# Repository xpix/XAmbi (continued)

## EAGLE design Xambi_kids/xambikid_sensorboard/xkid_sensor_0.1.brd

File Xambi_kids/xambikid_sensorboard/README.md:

XAmbi SensorBoard
----------------
By Frank Herrmann (xpixer@gmail.com)
<br/>

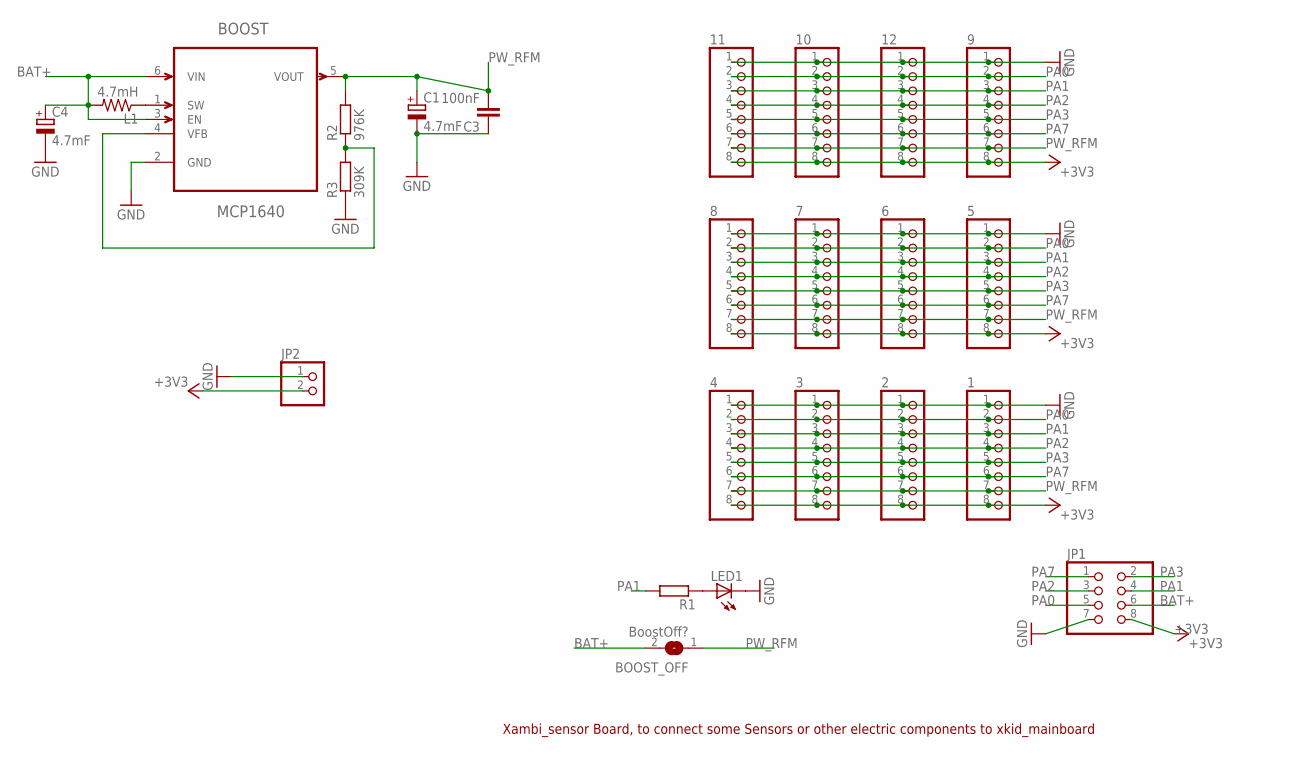
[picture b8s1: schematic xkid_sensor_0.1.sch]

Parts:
1, 2, 3, 4, 5, 6, 7, 8, 9, 10, 11, 12: PINHD-1X8_2.00; 1X08M
BOOST: MCP1640; SOT95P270X145-6N
BOOST_OFF: BoostOff?; SJ
C1, C4: 4.7mF; CT3216
C3: 100nF; C0805K
JP1: PINHD-2X4_2.54; 2X04
JP2: PINHD-1X2; 1X02
L1: 4.7mH; 0204/5
LED1: LEDCHIPLED_0805; CHIPLED_0805
R1: R-EU_R0805; R0805
R2: 976K; R0805
R3: 309K; R0805

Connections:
+3V3: 1.8, 2.8, 3.8, 4.8, 5.8, 6.8, 7.8, 8.8, 9.8, 10.8, 11.8, 12.8, JP1.8, JP2.2
BAT+: BOOST.3 (EN), BOOST.6 (VIN), BOOST_OFF.2, C4.+, JP1.6, L1.2
GND: 1.1, 2.1, 3.1, 4.1, 5.1, 6.1, 7.1, 8.1, 9.1, 10.1, 11.1, 12.1, BOOST.2 (GND), C1.-, C3.1, C4.-, JP1.7, JP2.1, LED1.C, R3.1
unnamed: LED1.A, R1.1
unnamed: BOOST.1 (SW), L1.1
unnamed: BOOST.4 (VFB), R2.1, R3.2
PA0: 1.2, 2.2, 3.2, 4.2, 5.2, 6.2, 7.2, 8.2, 9.2, 10.2, 11.2, 12.2, JP1.5
PA1: 1.3, 2.3, 3.3, 4.3, 5.3, 6.3, 7.3, 8.3, 9.3, 10.3, 11.3, 12.3, JP1.4, R1.2
PA2: 1.4, 2.4, 3.4, 4.4, 5.4, 6.4, 7.4, 8.4, 9.4, 10.4, 11.4, 12.4, JP1.3
PA3: 1.5, 2.5, 3.5, 4.5, 5.5, 6.5, 7.5, 8.5, 9.5, 10.5, 11.5, 12.5, JP1.2
PA7: 1.6, 2.6, 3.6, 4.6, 5.6, 6.6, 7.6, 8.6, 9.6, 10.6, 11.6, 12.6, JP1.1
PW_RFM: 1.7, 2.7, 3.7, 4.7, 5.7, 6.7, 7.7, 8.7, 9.7, 10.7, 11.7, 12.7, BOOST.5 (VOUT), BOOST_OFF.1, C1.+, C3.2, R2.2

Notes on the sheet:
Xambi_sensor Board, to connect some Sensors or other electric components to xkid_mainboard

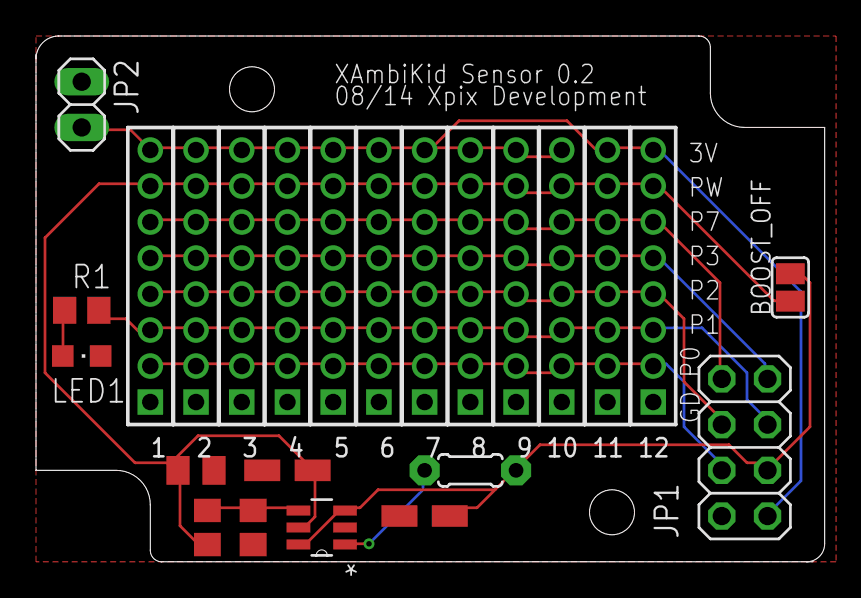
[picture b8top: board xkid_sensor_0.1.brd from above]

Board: 2 copper layers, 43.8 x 29.2 mm, 24 parts (0 on the bottom side), 12 nets.

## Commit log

2014-08-18 :tada: Added .gitattributes & .gitignore files
2014-08-18 Init commit
2015-01-08 Lot of updates
2015-01-08 Remove unused and temp files
2015-01-30 Lot of updates and new sensors
    - new mailbox sensor
    - update sensor mainboard
    - update sensor board
2015-01-30 Move old file to zip
2015-01-30 Remove some unused files
2015-01-30 add license
2015-02-02 add example schematic template for sensorboards
2015-02-02 Iniz readme for moisture board
2015-02-02 update example schema
2015-02-03 Fixes for mailbox and moisture sensor
    Change Threshold to 75 and calibrate every 15min and only 3 samples.
    Changes wait for minutes in moisture
2015-02-16 Last fixes for mailbox sensor
    - break 15 min and measure then (outside temp)
    - Threshold change to 40
    - display difference between calibration and measure value as second
    param
2015-03-02 fix and add docu for DS18B20
2015-03-02 add schematic for DHT11 Sensor
2015-03-03 - mailbox sensor doc and images
2015-03-03 Move not finished or ideas to prototype folder
2015-03-03 change template for sensor images
2015-03-03 - pic prototype
2015-03-03 - Move all gateway stuff to extra directory
2015-03-04 add xpix libraries to xambi for compile
2015-03-05 - add some pics for doku revert to jeelab
2015-03-06 - fix first call
2015-03-06 rotate pic
2015-03-06 - Add readme and pics to new board with booster and infrared
2015-03-18 add booster to mainboard, add IR LED for ir communication
2015-04-10 mailbox update
    Threshold set to 30
    first tests with infrared
2015-04-16 Create gh-pages branch via GitHub
2015-08-03 Add new board for Xambi Arduino Mini Pro
    Add example for esp8266-wifi370
    Add some examples for
